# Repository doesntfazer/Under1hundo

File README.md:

100x100mm split keyboard, for cheap manufacturing by PCBway. reversible, and hot swap.
The 2040 zero is soldered face down when facing the left side of the board.

Parts list.

2x PJ-320A TRRS jacks

2x RP2040 zero

2x Plates, Left and right (Optional: 3d printed)

2x Case Left and right (Optional: 3d printed)

8x M2 heat set inserts (only needed if printing case)

8x M2 8mm-10mm Screws (only needed if printing case)

34x hot swap sockets

34x Cherry MX style switches

Check out the [firmware](https://github.com/doesntfazer/Keyboard-Dweebs-Firmware-repository/tree/main/VIAL-QMK/under1hundo)

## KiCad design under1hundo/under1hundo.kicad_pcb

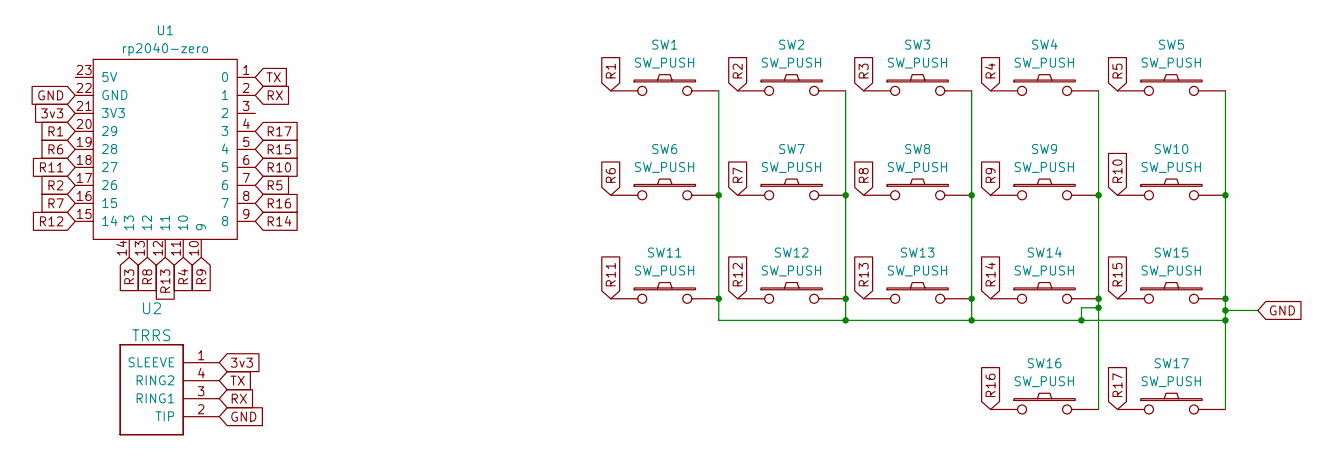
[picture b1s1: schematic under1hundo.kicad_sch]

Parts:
SW1, SW2, SW3, SW4, SW5, SW6, SW7, SW8, SW9, SW10, SW11, SW12, SW13, SW14, SW15, SW16, SW17: SW_PUSH; CherryMX_MidHeight_Hotswap
U1: rp2040-zero; rp2040-zero-tht-nocut
U2: TRRS; TRRS-PJ-320A-rev - Copy

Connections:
3v3: U1.21 (3V3), U2.1 (SLEEVE)
GND: SW1.2, SW2.2, SW3.2, SW4.2, SW5.2, SW6.2, SW7.2, SW8.2, SW9.2, SW10.2, SW11.2, SW12.2, SW13.2, SW14.2, SW15.2, SW16.2, SW17.2, U1.22 (GND), U2.2 (TIP)
R1: SW1.1, U1.20 (29)
R2: SW2.1, U1.17 (26)
R3: SW3.1, U1.14 (13)
R4: SW4.1, U1.11 (10)
R5: SW5.1, U1.7 (6)
R6: SW6.1, U1.19 (28)
R7: SW7.1, U1.16 (15)
R8: SW8.1, U1.13 (12)
R9: SW9.1, U1.10 (9)
R10: SW10.1, U1.6 (5)
R11: SW11.1, U1.18 (27)
R12: SW12.1, U1.15 (14)
R13: SW13.1, U1.12 (11)
R14: SW14.1, U1.9 (8)
R15: SW15.1, U1.5 (4)
R16: SW16.1, U1.8 (7)
R17: SW17.1, U1.4 (3)
RX: U1.2 (1), U2.3 (RING1)
TX: U1.1 (0), U2.4 (RING2)

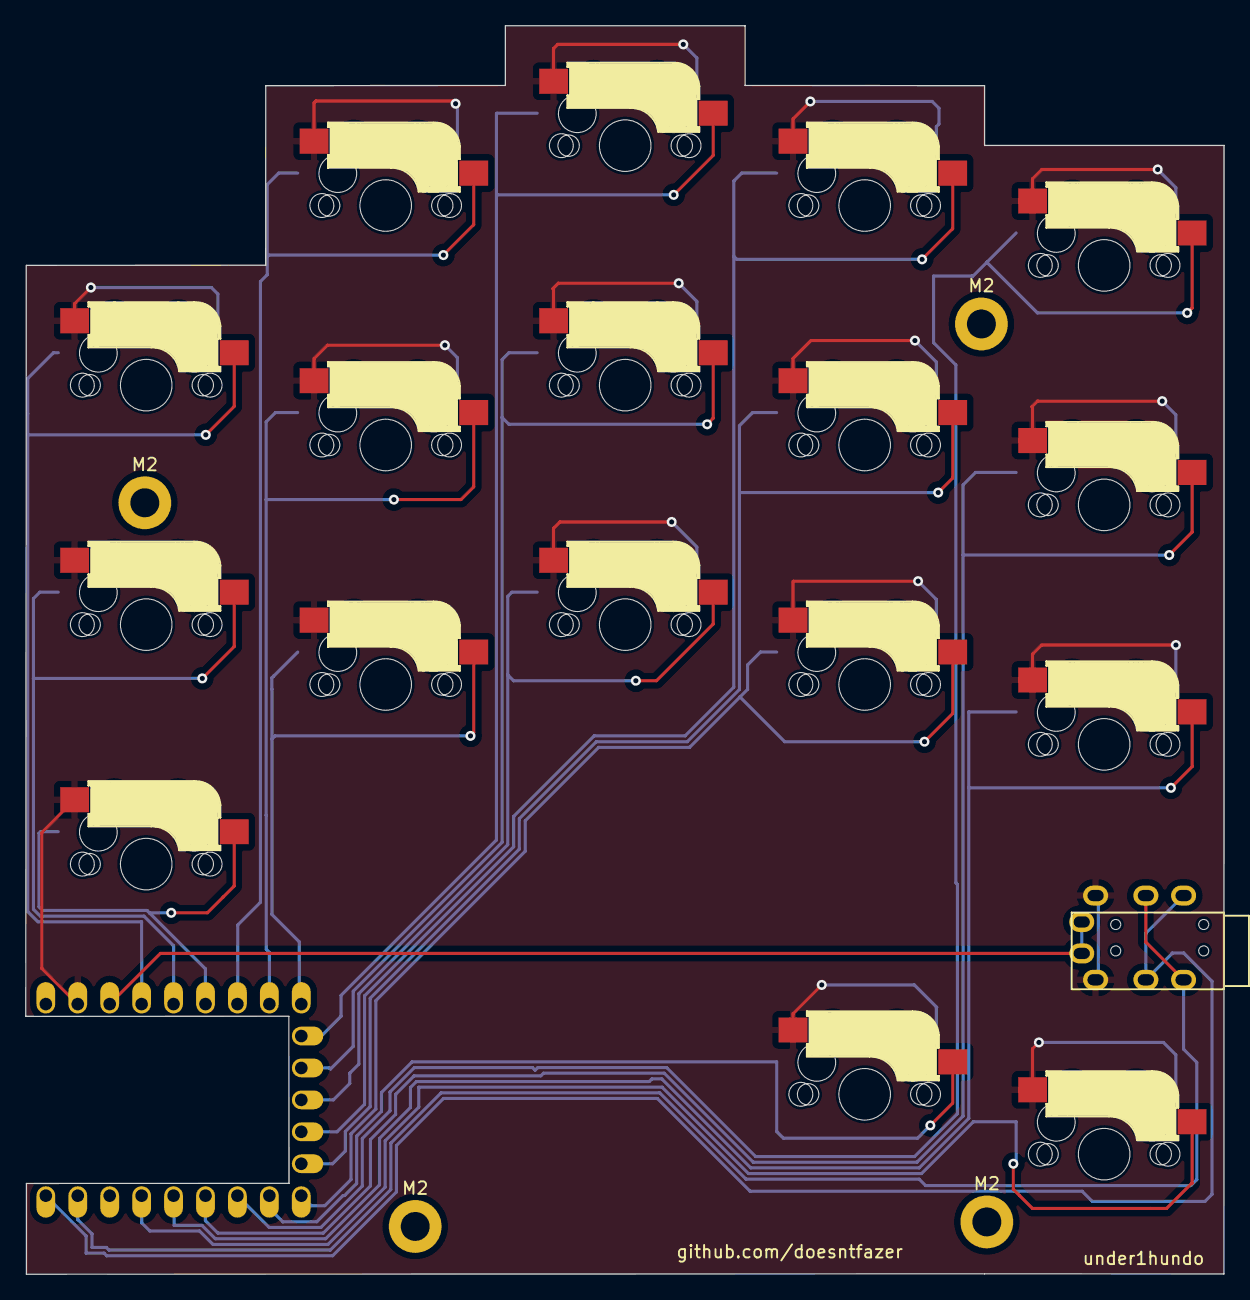
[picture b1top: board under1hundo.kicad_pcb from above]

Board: 2 copper layers, 95.3 x 99.3 mm, 23 parts (1 on the bottom side), 21 nets.

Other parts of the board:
M2, M2#2, M2#3, M2#4: M2_Hole_TH

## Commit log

2024-08-07 Files
